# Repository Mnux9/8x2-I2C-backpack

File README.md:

# 8x2-I2C-backpack
I2C backpack for small 8x2 character lcds

More info at: [https://mnux.xyz/posts/https://mnux.xyz/posts/uI2Cbackpack.htm](https://mnux.xyz/posts/uI2Cbackpack.htm)

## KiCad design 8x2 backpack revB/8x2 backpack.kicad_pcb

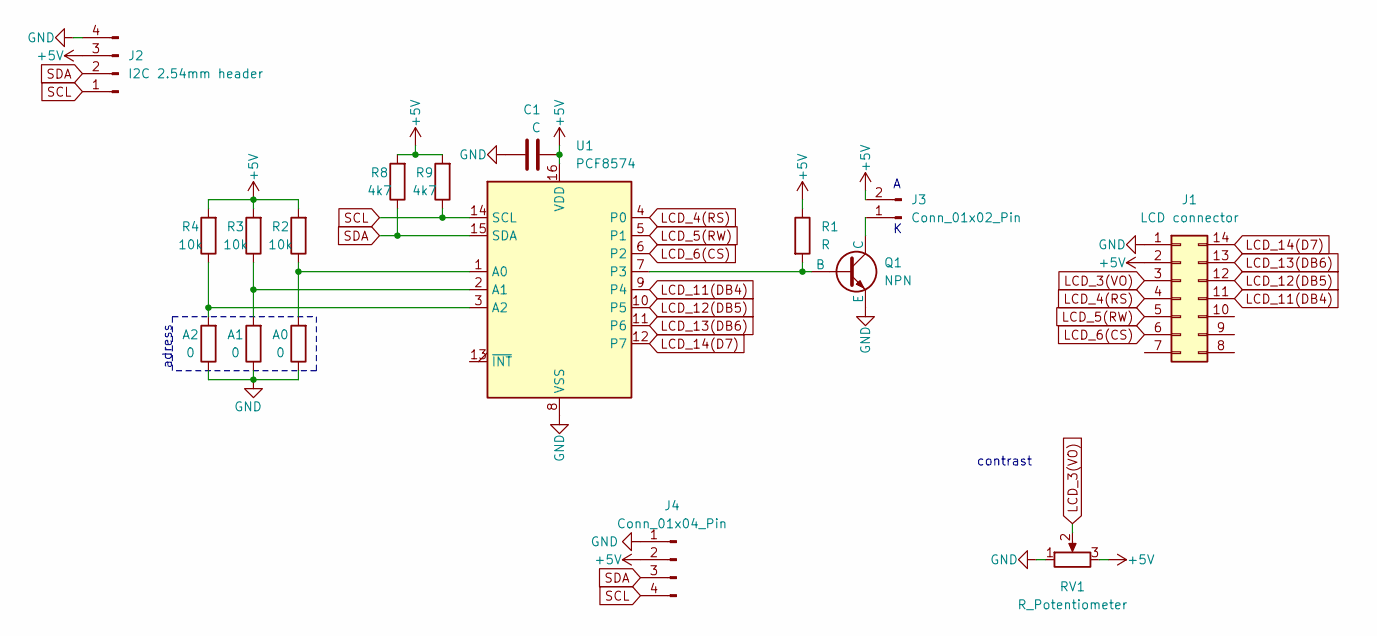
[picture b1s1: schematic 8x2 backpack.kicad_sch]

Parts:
A0, A1, A2: 0; R_0805_2012Metric
C1: C; C_0805_2012Metric
J1: LCD connector; PinHeader_2x07_P2.54mm_Vertical
J2: I2C 2.54mm header; PinHeader_1x04_P2.54mm_Vertical
J3: Conn_01x02_Pin; PinHeader_1x02_P2.54mm_Vertical
J4: Conn_01x04_Pin; JST_SH_SM04B-SRSS-TB_1x04-1MP_P1.00mm_Horizontal
Q1: NPN; SOT-23-3
R1: R; R_0805_2012Metric
R2, R3, R4: 10k; R_0805_2012Metric
R8, R9: 4k7; R_0805_2012Metric
RV1: R_Potentiometer; Potentiometer_Bourns_3362P_Vertical
U1: PCF8574; SO-16_5.3x10.2mm_P1.27mm

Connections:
+5V: C1.2, J1.2, J2.3, J3.2, J4.2, R1.1, R2.2, R3.2, R4.2, R8.2, R9.2, RV1.3, U1.16 (VDD)
GND: A0.1, A1.1, A2.1, C1.1, J1.1, J2.4, J4.1, J4.MP, Q1.3 (E), RV1.1, U1.8 (VSS)
LCD_3(VO): J1.3, RV1.2
LCD_4(RS): J1.4, U1.4 (P0)
LCD_5(RW): J1.5, U1.5 (P1)
LCD_6(CS): J1.6, U1.6 (P2)
LCD_11(DB4): J1.11, U1.9 (P4)
LCD_12(DB5): J1.12, U1.10 (P5)
LCD_13(DB6): J1.13, U1.11 (P6)
LCD_14(D7): J1.14, U1.12 (P7)
unnamed: J3.1, Q1.1 (C)
unnamed: Q1.2 (B), R1.2, U1.7 (P3)
unnamed: A0.2, R2.1, U1.1 (A0)
unnamed: A1.2, R3.1, U1.2 (A1)
unnamed: A2.2, R4.1, U1.3 (A2)
SCL: J2.1, J4.4, R9.1, U1.14 (SCL)
SDA: J2.2, J4.3, R8.1, U1.15 (SDA)

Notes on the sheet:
adress
contrast

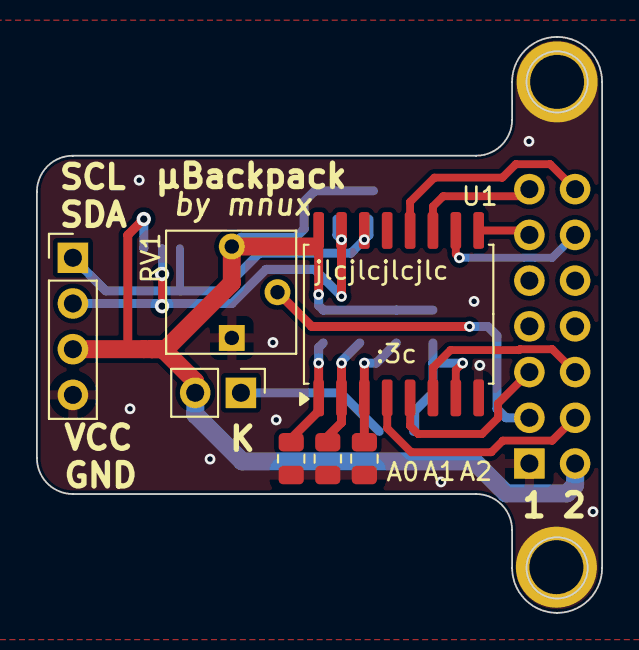
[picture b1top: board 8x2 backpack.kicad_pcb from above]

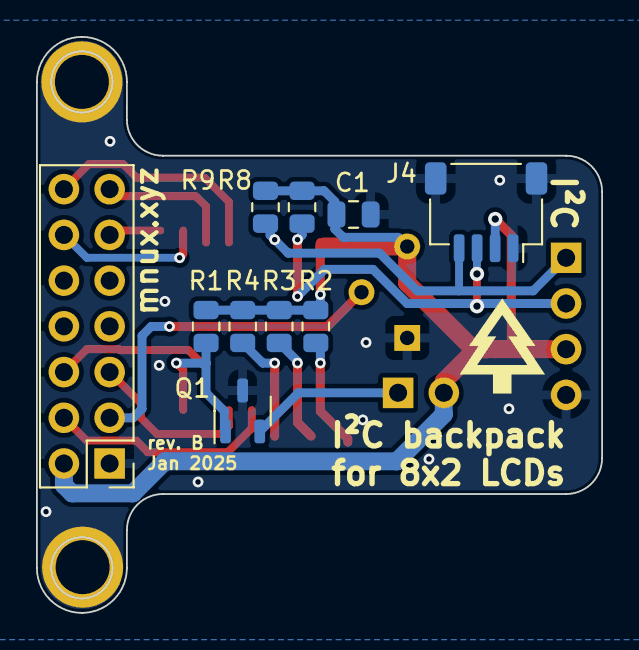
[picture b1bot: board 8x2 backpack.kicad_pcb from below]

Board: 2 copper layers, 31.4 x 32.0 mm, 17 parts (10 on the bottom side), 17 nets.

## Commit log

2025-01-13 add revision A
2025-01-13 add rev B
2025-01-13 add link to README.md
